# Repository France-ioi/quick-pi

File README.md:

# quick-pi
Tools to enable programming a Raspberry Pi from the QuickAlgo environment

# How to setup

* Download the latest Raspbian Buster Lite (no GUI needed) version from https://www.raspberrypi.org/downloads/raspbian/, follow the instructions on how to write the image to an SD card here https://www.raspberrypi.org/documentation/installation/installing-images/README.md.

* If you are planing to make this a production ready image reinsert the SD card into the machine you used to write it and go to the drive. You will find a cmdline.txt file. Open it and delete `init=/usr/lib/raspi-config/init_resize.sh
` from the end of the command line. This will prevent the filesystem to be resized to fill the whole size of your sd card.

* Boot the Raspberry Pi (connect a keyboard and display), login with the default pi/raspbian user password.

* Create a 100M partition after the root partition to store the installed program (the root partition is read only):

```
echo -e "n\n\n\n4292608\n+100M\nw\nq\n" | fdisk /dev/mmcblk0
partprobe

mkfs.ext4 /dev/mmcblk0p3
mkdir /mnt/data
chown pi.pi /mnt/data/
echo "/dev/mmcblk0p3 /mnt/data ext4 defaults 0 2" >> /etc/fstab
```

* Run `sudo raspi-config` and enable SSH (for easier remote management and setup WiFi), also enable I2C (Needed for analog sensors).

* Install the required dependencies by doing: `sudo apt-get install python3-flask python3-pip python3-rpi.gpio gunicorn3 dos2unix python3-pexpect python3-smbus pigpio python3-pigpio  bluez-tools dnsmasq bridge-utils python3-pil hostapd` 

then:
`sudo pip3 install flask-cors Flask-Sockets luma.oled adafruit-circuitpython-vl53l0x`. 

also:
`sudo systemctl enable pigpiod`

and:
`sudo systemctl unmask hostapd`

* Copy the contents of the `server` directory into /home/pi/quickpi/ in the Raspberry Pi using scp. This is a flask webapp that will run the programs in the Raspberry Pi.

# How to create a production ready image

First run all of the above steps then:

* Add `dtoverlay=dwc2,dr_mode=peripheral` to the bottom of /boot/config.txt

* Add `modules-load=dwc2,g_ether` in /boot/cmdline.txt right next to `rootwait`. Don't introduce new lines into this file.

* Edit /lib/systemd/system/pigpiod.service to change pigpiod command line to the following `/usr/bin/pigpiod -n 127.0.0.1 -l -m -x -1`

* Add the following command to /etc/rc.local:

```
/home/pi/quickpi/scripts/start.sh &
```

* Edit the file /lib/systemd/system/raspberrypi-net-mods.service so it look like this:

```
[Unit]
Description=Copy user wpa_supplicant.conf
Before=dhcpcd.service
After=systemd-rfkill.service

[Service]
Type=oneshot
RemainAfterExit=yes
ExecStart=/home/pi/quickpi/scripts/setupwifi.sh
ExecStartPost=/bin/chmod 600 /etc/wpa_supplicant/wpa_supplicant.conf
ExecStartPost=/usr/sbin/rfkill unblock wifi

[Install]
WantedBy=multi-user.target
```

* Delete the wpa_supplicant config file and link it to /tmp like with these commands:

```
rm /etc/wpa_supplicant/wpa_supplicant.conf
ln -s /tmp/wpa_supplicant.conf /etc/wpa_supplicant/wpa_supplicant.conf
```

* Move the dhcpcd config and link it to /tmp:

```
mv /etc/dhcpcd.conf /etc/dhcpcd.conf.template
ln -s /tmp/dhcpcd.conf /etc/dhcpcd.conf
```

Same with hostapd config file:

```
rm -f /etc/hostapd/hostapd.conf 
ln -s /tmp/hostapd.conf /etc/hostapd/hostapd.conf
```

* Add the following to the bottom of /etc/dhcpcd.conf.template

```
interface usb0
static ip_address=192.168.233.1

interface pan0
static ip_address=192.168.233.2

denyinterfaces ap0
interface ap0
nohook wpa_supplicant

```

* Edit /etc/dnsmasq.conf so that this is the entiere contents:

```
interface=usb0
interface=ap0
interface=pan0
dhcp-range=192.168.233.10,192.168.233.230,2h
dhcp-option=usb0,3
dhcp-option=usb0,6
address=/#/192.168.233.3
```

* Edit /etc/default/dnsmasq to add at the bottom:

```
DNSMASQ_EXCEPT=lo
```

* Delete /var/lib/ and link it to /tmp
```
rm -rf /var/lib/misc
ln -s /tmp /var/lib/misc 
```

* Create a dummy quickpi.txt file in /boot with the following contents:

```
SSID=wifiname
PASSWORD=wifipassword
STATICNETWORK=1
STATICIPADDR=192.168.1.31
STATICGATEWAY=192.168.1.1
STATICDNS=8.8.8.8

NAME=quickpi1
SCHOOL=schoolkey
SCHOOLPASSWORD=schoolpassword
```

* Download Adafruit script to make the filesystem readonly: `wget https://raw.githubusercontent.com/adafruit/Raspberry-Pi-Installer-Scripts/master/read-only-fs.sh; sudo bash read-only-fs.sh`. Answer N to "Enable boot-time jumper", "Install GPIO-halt utility" and `Enable kernel panic watchdog` so none of those is enabled.

* Shutdown the Raspberry Pi using `sudo halt`. Remove the raspberry pi and take an image of the SD card of the same size plus 100M (add a bit to be sure) of the original Raspbian Image you started with.

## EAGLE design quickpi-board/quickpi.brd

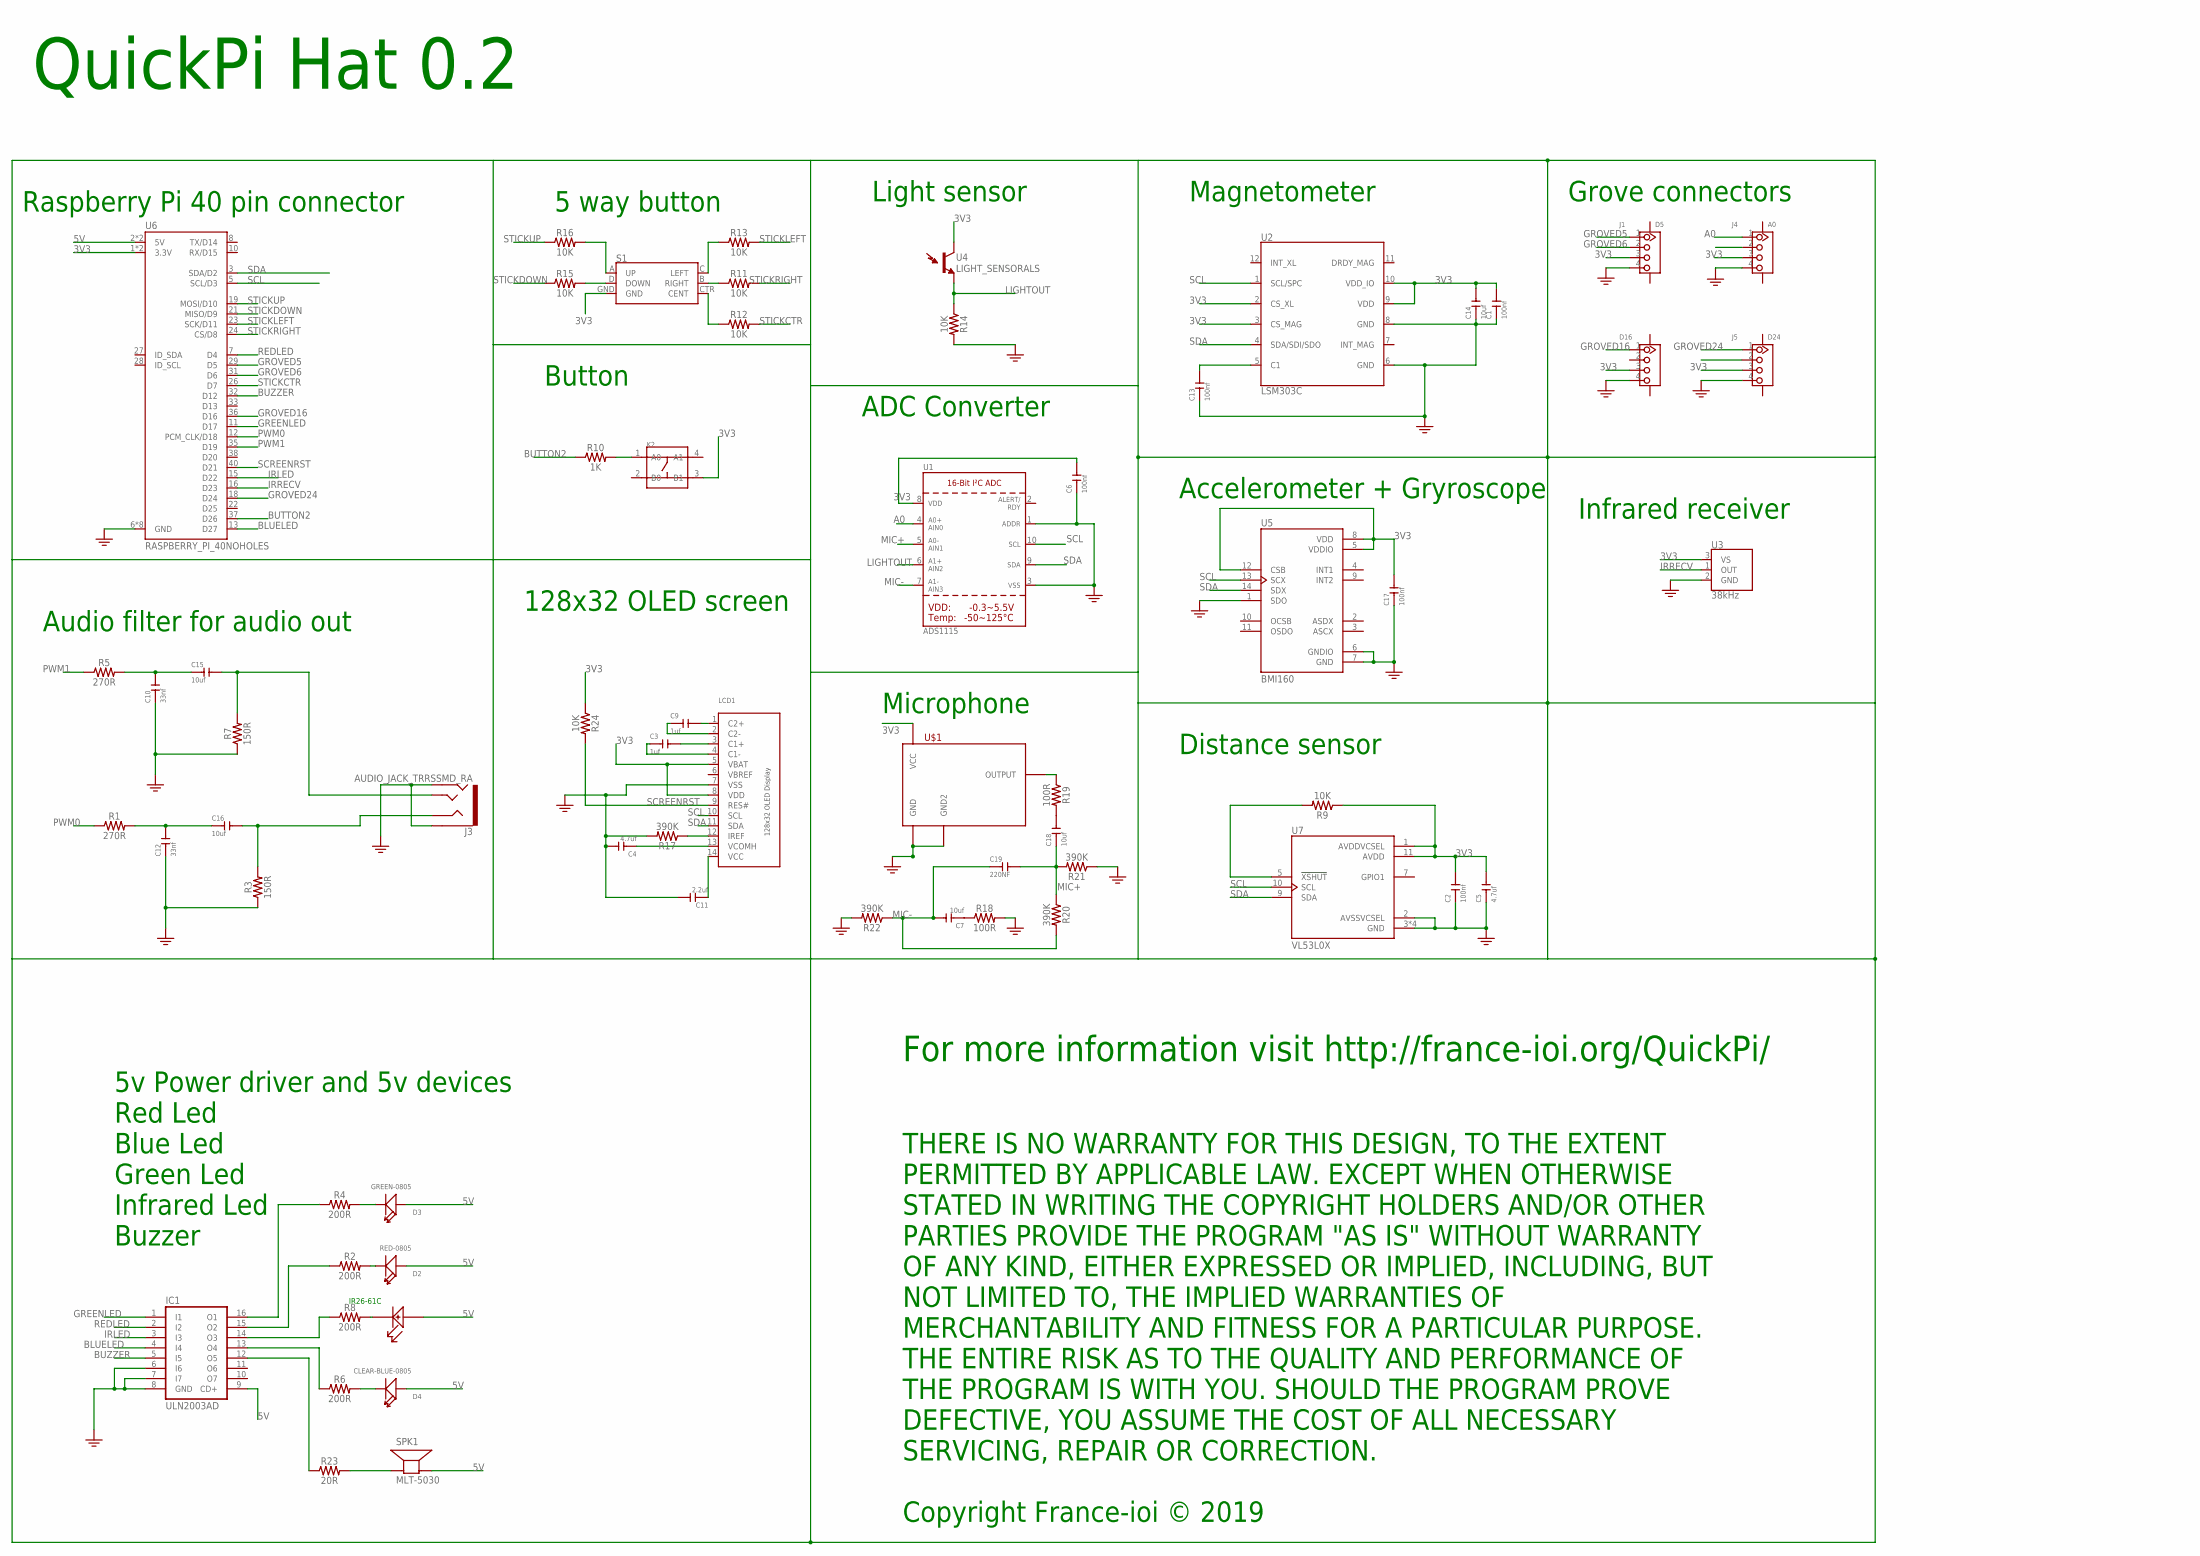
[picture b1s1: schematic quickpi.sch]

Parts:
C1, C2, C6, C13, C17: 100nf; C0402
C3, C9: 1uf; C0402
C4, C5: 4.7uf; C0402
C7, C14, C15, C16, C18: 10uf; C0402
C10, C12: 33nf; C0402
C11: 2.2uf; C0402
C19: 220NF; C0402
D2: RED-0805; LED-0805
D3: GREEN-0805; LED-0805
D4: CLEAR-BLUE-0805; LED-0805
D16: GROVE-CONNECTOR-SMD-90D(4+2P-2.0); HW4-SMD-2.0-90D
IC1: ULN2003AD; SO16
J1: D5; HW4-SMD-2.0-90D
J3: AUDIO_JACK_TRRSSMD_RA; AUDIO_JACK_3.5MM_TRRS_SMD_RA
J4: A0; HW4-SMD-2.0-90D
J5: D24; HW4-SMD-2.0-90D
K2: SMD-SWITCH-TACTILE-SPST-NO(4P-D6.0MM); SW4-SMD-6.0X6.0X5.0MM
LCD1: DISP_OLED_UG-2832HSWEG02; UG-2832HSWEG02_WRAPUNDER
R1, R5: 270R; 0402
R2, R4, R6, R8: 200R; 0402
R3, R7: 150R; 0402
R9, R11, R12, R13, R14, R15, R16, R24: 10K; 0402
R10: 1K; 0402
R17, R20, R21, R22: 390K; 0402
R18, R19: 100R; 0402
R23: 20R; 0402
S1: JOYSTICK_MINI
SPK1: MLT-5030; SMT-0540-S-R
U1: ADS1015; MSOP10
U2: LSM303C; LGA-12
U3: 38kHz; TSOP382
U4: LIGHT_SENSORALS; ALS-PT19
U5: BMI160; PQFN50P300X250X88-14N
U6: RASPBERRY_PI_40NOHOLES; RASPBERRY_PI_SHIELD_NOHOLES
U7: VL53L0X; SENSOR_VL53L0X
U$1: MEMS_MIC_SPU0414HR5H-SB; CSP-4PIN
U$2: IR26-61C/L302/TR8

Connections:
3V3: C1.2, C2.2, C5.2, C6.2, C14.2, C17.2, D16.3, J1.3, J4.3, J5.3, K2.3 (B1), LCD1.5 (VBAT), LCD1.8 (VDD), R9.1, R24.1, S1.GND, U1.8 (VDD), U2.2 (CS_XL), U2.3 (CS_MAG), U2.9 (VDD), U2.10 (VDD_IO), U3.3 (VS), U4.C (C1), U5.5 (VDDIO), U5.8 (VDD), U5.12 (CSB), U6.1 (3.3V), U6.17 (3.3V), U7.1 (AVDDVCSEL), U7.11 (AVDD), U$1.VCC
5V: D2.+, D3.+, D4.+, IC1.9 (CD+), SPK1.+ (-), U6.2 (5V), U6.4 (5V), U$2.VCC (GND)
A0: J4.1, U1.4 (AIN0)
BLUELED: IC1.4 (I4), U6.13 (D27)
BUTTON2: R10.1, U6.37 (D26)
BUZZER: IC1.5 (I5), U6.32 (D12)
GND: C1.1, C2.1, C4.2, C5.1, C6.1, C10.1, C11.2, C12.1, C13.1, C14.1, C17.1, D16.4, IC1.6 (I6), IC1.7 (I7), IC1.8 (GND), J1.4, J3.EARTH, J3.RING2, J4.4, J5.4, LCD1.7 (VSS), R3.1, R7.1, R14.2, R17.2, R18.2, R21.1, R22.2, U1.1 (ADDR), U1.3 (VSS), U2.6 (GND), U2.8 (GND), U3.2 (GND), U5.1 (SDO), U5.6 (GNDIO), U5.7 (GND), U6.6 (GND), U6.9 (GND), U6.14 (GND), U6.20 (GND), U6.25 (GND), U6.30 (GND), U6.34 (GND), U6.39 (GND), U7.2 (AVSSVCSEL), U7.3 (GND), U7.4 (GND), U7.6 (GND), U7.12 (GND), U$1.GND, U$1.GND2
GREENLED: IC1.1 (I1), U6.11 (D17)
GROVED5: J1.1, U6.29 (D5)
GROVED6: J1.2, U6.31 (D6)
GROVED16: D16.1, U6.36 (D16)
GROVED24: J5.1, U6.18 (D24)
IRLED: IC1.3 (I3), U6.15 (D22)
IRRECV: U3.1 (OUT), U6.16 (D23)
LIGHTOUT: R14.1, U1.6 (AIN2), U4.E (E1)
MIC+: C18.1, C19.2, R20.1, R21.2, U1.5 (AIN1)
MIC-: C7.2, C19.1, R20.2, R22.1, U1.7 (AIN3)
unnamed: C3.2, LCD1.3 (C1+)
unnamed: C16.2, J3.RING1, R3.2
unnamed: D4.-, R6.2
unnamed: IC1.13 (O4), R6.1
unnamed: IC1.15 (O2), R2.1
unnamed: R8.2, U$2.GND (VCC)
unnamed: C15.2, J3.TIP, R7.2
unnamed: IC1.16 (O1), R4.1
unnamed: D3.-, R4.2
unnamed: C10.2, C15.1, R5.2
unnamed: C12.2, C16.1, R1.2
unnamed: D2.-, R2.2
unnamed: R9.2, U7.5 (!XSHUT)
unnamed: C3.1, LCD1.4 (C1-)
unnamed: C13.2, U2.5 (C1)
unnamed: R19.1, U$1.OUTPUT
unnamed: K2.1 (A0), R10.2
unnamed: IC1.14 (O3), R8.1
unnamed: R13.1, S1.C (LEFT)
unnamed: R11.1, S1.B (RIGHT)
unnamed: IC1.12 (O5), R23.1
unnamed: R23.2, SPK1.- (+)
unnamed: C9.2, LCD1.1 (C2+)
unnamed: C9.1, LCD1.2 (C2-)
unnamed: LCD1.12 (IREF), R17.1
unnamed: R12.1, S1.CTR (CENT)
unnamed: C11.1, LCD1.14 (VCC)
unnamed: R15.2, S1.D (DOWN)
unnamed: R16.2, S1.A (UP)
unnamed: C4.1, LCD1.13 (VCOMH)
unnamed: C18.2, R19.2
unnamed: C7.1, R18.1
PWM0: R1.1, U6.12 (PCM_CLK/D18)
PWM1: R5.1, U6.35 (D19)
REDLED: IC1.2 (I2), U6.7 (D4)
SCL: LCD1.10 (SCL), U1.10 (SCL), U2.1 (SCL/SPC), U5.13 (SCX), U6.5 (SCL/D3), U7.10 (SCL)
SCREENRST: LCD1.9 (RES#), R24.2, U6.40 (D21)
SDA: LCD1.11 (SDA), U1.9 (SDA), U2.4 (SDA/SDI/SDO), U5.14 (SDX), U6.3 (SDA/D2), U7.9 (SDA)
STICKCTR: R12.2, U6.26 (D7)
STICKDOWN: R15.1, U6.21 (MISO/D9)
STICKLEFT: R13.2, U6.23 (SCK/D11)
STICKRIGHT: R11.2, U6.24 (CS/D8)
STICKUP: R16.1, U6.19 (MOSI/D10)
VBREF: LCD1.6 (VBREF)

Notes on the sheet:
Audio filter for audio out
Raspberry Pi 40 pin connector
5 way button
Button
128x32 OLED screen
Light sensor
ADC Converter
Microphone
Magnetometer
Accelerometer + Gryroscope
Distance sensor
Grove connectors
Infrared receiver
5v Power driver and 5v devices Red Led Blue Led Green Led Infrared Led Buzzer
THERE IS NO WARRANTY FOR THIS DESIGN, TO THE EXTENT PERMITTED BY APPLICABLE LAW. EXCEPT WHEN OTHERWISE STATED IN WRITING THE COPYRIGHT HOLDERS AND/OR OTHER PARTIES PROVIDE THE PROGRAM "AS IS" WITHOUT WARRANTY OF ANY KIND, EITHER EXPRESSED OR IMPLIED, INCLUDING, BUT NOT LIMITED TO, THE IMPLIED WARRA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
Copyright France-ioi © 2019
QuickPi Hat 0.2
For more information visit http://france-ioi.org/QuickPi/
IR26-61C

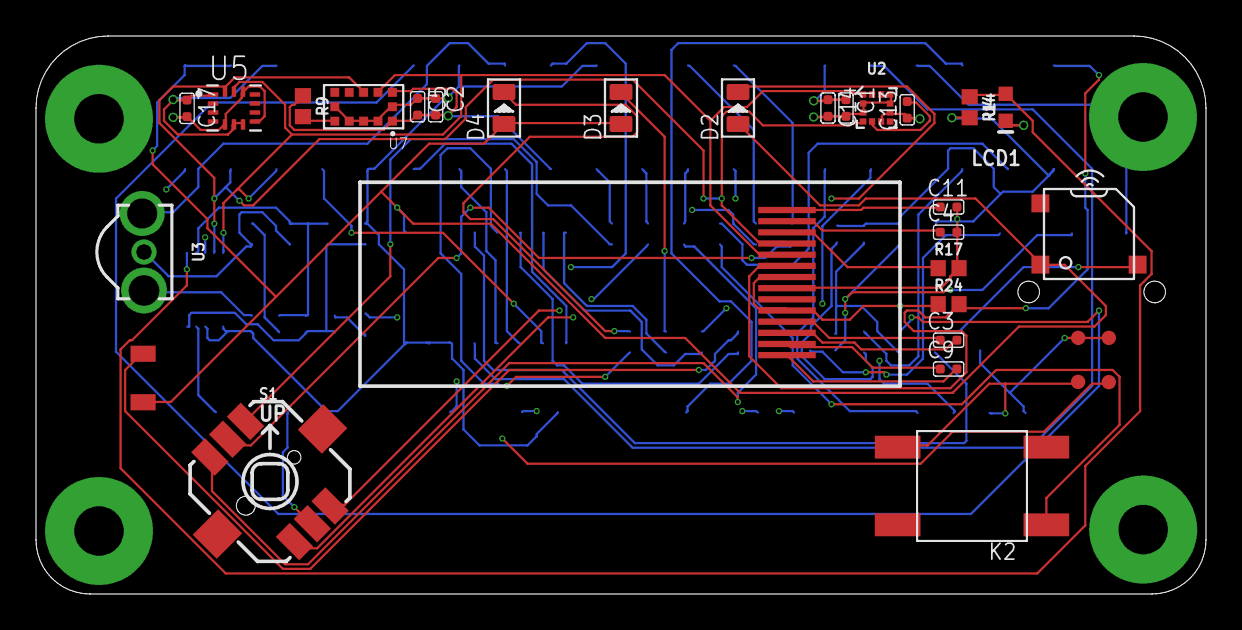
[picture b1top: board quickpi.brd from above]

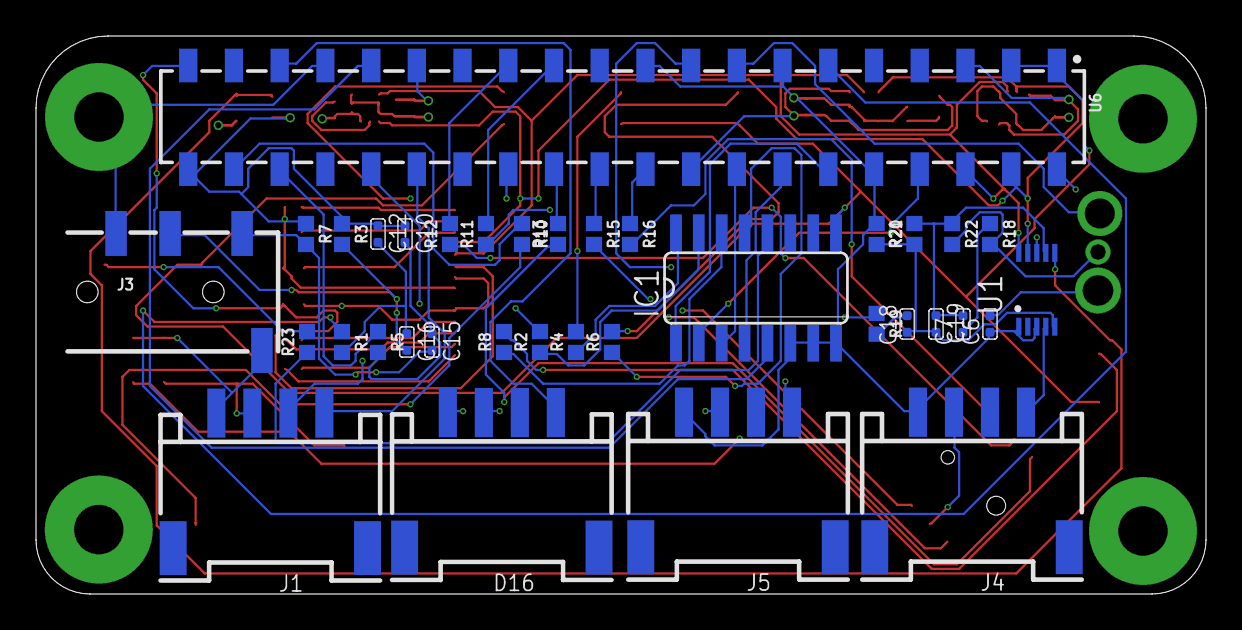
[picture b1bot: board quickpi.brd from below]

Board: 4 copper layers, 65.0 x 31.0 mm, 64 parts (36 on the bottom side), 60 nets.

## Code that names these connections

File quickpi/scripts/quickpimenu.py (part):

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LEFT_PIN=11
RIGHT_PIN=8
CENTER_PIN=7
BUTTON2_PIN=26
BUZZER_PIN=12
REDLED_PIN=4

RUNAUTOTEST = 1
LEDSHOW = 2
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GPIO.setup(LEFT_PIN, GPIO.IN, pull_up_down=GPIO.PUD_DOWN)
GPIO.setup(RIGHT_PIN, GPIO.IN, pull_up_down=GPIO.PUD_DOWN)
GPIO.setup(CENTER_PIN, GPIO.IN, pull_up_down=GPIO.PUD_DOWN)
GPIO.setup(BUTTON2_PIN, GPIO.IN, pull_up_down=GPIO.PUD_DOWN)
GPIO.setup(REDLED_PIN, GPIO.OUT)
GPIO.output(REDLED_PIN, GPIO.LOW)


pi = pigpio.pi()
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	while keepgoing:
		for button in buttons:
			if GPIO.input(button):
				changePassiveBuzzerState(BUZZER_PIN, 1)
				GPIO.output(REDLED_PIN, GPIO.HIGH)
				time.sleep(0.050)
				changePassiveBuzzerState(BUZZER_PIN, 0)
				GPIO.output(REDLED_PIN, GPIO.LOW)
				return button
		keepgoing = wait
		time.sleep(0.05)
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	start = time.time()
	oldtimeleft = asktocancel
	while True:
		retval = waitForButton([UP_PIN, DOWN_PIN, LEFT_PIN, RIGHT_PIN, CENTER_PIN, BUTTON2_PIN], False)

		if retval is not None:
			displayText("", "", "")
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
	device.display(oledimage)

	waitForButton([UP_PIN, DOWN_PIN, LEFT_PIN, BUTTON2_PIN])

currentMenuPos = 0
currentMenu = main_menu
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		print(currentMenu[currentMenuPos])

	time.sleep(0.2)
	pressed = waitForButton([UP_PIN, DOWN_PIN, LEFT_PIN, BUTTON2_PIN])
	if pressed == DOWN_PIN:
		if currentMenu is not None:
			currentMenuPos = currentMenuPos + 1
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			currentMenu = menuStack.pop()
			currentTitle = titleStack.pop()

	elif pressed == BUTTON2_PIN:
		if currentMenu is None:
			continue

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					pass

				drawMenu("Compass reset", "completed", False)
				waitForButton([UP_PIN, DOWN_PIN, LEFT_PIN, BUTTON2_PIN])

			elif menuoption == RUNBOARDTEST:
				os.system("python3 /home/pi/quickpi/testsuite/fulltest.py")

				waitForButton([UP_PIN, DOWN_PIN, LEFT_PIN, BUTTON2_PIN])

			elif menuoption == RUNAUTOUPDATE:
				file = open('/home/pi/quickpi/version',mode='r')
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
				keepgoing = False
				while True:
					pressed = waitForButton([LEFT_PIN, BUTTON2_PIN], False)
					if pressed == LEFT_PIN:
						keepgoing = False
						break
					elif pressed == BUTTON2_PIN:
						keepgoing = True
						break

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
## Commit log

2018-12-23 fix typo
2019-01-02 Initial version
2019-01-02 Quick script to create the wifi setup
2019-01-02 Document how to make a production image
2019-01-02 Missing file
2019-01-04 Implement program output and locking by ip address
2019-01-04 Add mechanism to setup an static ip address
2019-01-11 Implement command mode over websockets. Also move all of the previous interface to websockets as well.
2019-01-12 Username lock
2019-01-18 implement functions for some of the grove sensors and update some dependencies into the README
2019-02-17 Add full ip address setup to the wifi scripts/setupwifi.sh Fix cleanup script for grove pi. Updates to server. Install script.
2019-03-05 add ping script
2019-03-05 actually read the values from the file
2019-03-08 siwtch the server to return json
2019-03-14 Update instructions for bluetooth and usb connections
2019-04-02 Script diagnostics
2019-09-06 Update instructions for raspbian buster
2019-09-06 test suite
2020-03-08 Latest updates
2020-03-08 quick pi board
2020-03-11 Latest changes
2020-03-11 latest fixes
2020-03-12 More fixes
2020-03-13 Add first version of qt-client
2020-03-13 Update 6: Integrated tunnel
2020-03-13 Ask for reboot after saving settings. Send a clsoed message when we are closing the session.
2020-03-15 Switch qt-client to websocket-client library
2020-03-17 Include the websocket-client library for the new tunnel script.
2020-03-18 Run the tunnel under the pi user as it has the proxy variables already setup.
2020-03-18 Only start menu if there's no installed program. Add testbed task Moved testsuite
2020-03-18 Add test to menu
2020-03-20 Translate some of the curl errors Add about menu Fix typo Show all possible different ip addresses
2020-03-22 Remove pexpect's delay, this makes things much faster.
2020-03-23 Add version. Support multiple commands in a single package.
2020-03-25 Use importModules(quickpi-connection) rathern than directly include the javascript file.
2020-04-22 grove->grovepi
2020-04-24 Update trough the web interface
2020-07-21 Update fixes
2020-07-21 quickPi: Change string to fit screen
2020-07-21 Changes to the update script
2020-07-21 Make url unique to avoid cache
2020-07-21 Small fixes
2020-08-04 Use a different method to parse config file Don't remove spaces from wifi password Blink and beep when button is pressed in menu
2020-08-04 http://quick-pi.org/update/version->https://quick-pi.org/update/version Fix standalone update
2020-08-09 Latest
2020-08-16 Fix showtext.py for the quickpi board Change server protocol to minimize python lib uploads. Don't call showtext.py from ping.sh Show the type of ip address in the quickpi menu in the header.js Add s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
2020-08-21 Latest changes: - Login password to config page - Update system password to config password - Menu to enable bluetooth temporary
2020-08-23 Update system password to web config password and hash it on first boot
2020-11-12 latest changes. Bypass password settings and extra diagnosis log
2020-12-30 New autodetection code
2021-02-06 Small testbed changes
2021-03-18 Update test for new board
2021-03-21 Restore buttons functionality. Return proper error status when not authenticated.
2021-04-18 Misc bug fixes
2021-06-15 Test fixes
2021-06-16 Update quickpi lib
2021-10-05 Add option in the menu to reset compass calibration

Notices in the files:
parts and their libraries:
SparkFun-Sensors: Licensing: Creative Commons ShareAlike 4.0 International - https://creativecommons.org/licenses/by-sa/4.0
microbuilder-eited: This work is placed in the public domain, and may be freely used for commercial and non-commercial work with the following conditions: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
